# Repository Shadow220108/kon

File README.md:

<h1 align="center">
<br>

<br>
kon
<br>
</h1>

<h3 align="center">

A little ESP32-S3 e-ink reader for books on a microSD card 

</h3>

<div align="center">

</div>

kon is a small e-reader I designed from scratch. It has a 4.26 inch 800 x 480 e-ink screen, reads .txt books off a microSD card, and you flip pages with 4 buttons on the side. It runs off a LiPo battery that charges over USB-C, and since e-ink only uses power when the page changes, the battery lasts ages. The PCB is made in KiCad and the case in Fusion 360.

The render was designed in blender :p

## Journals
Journals were written after I was done with the project with my best memory and a help of AI, it has a total of about 46 hours! 

## Features

- ESP32-S3-WROOM-1-N16R8, 16MB flash, 8MB PSRAM, WiFi and Bluetooth, native USB
- 4.26 inch GDEY0426T82 e-paper (800 x 480, SSD1677) on a 24 pin FPC
- On board high voltage boost circuit for the e-paper
- microSD in 4 bit mode, with its own power switch so it's fully off in sleep
- PREV, NEXT, MENU and BACK buttons that can wake it from deep sleep
- Single cell LiPo with an MCP73831 charger (500mA), red / green charge LEDs
- Power path that runs from USB when plugged in and from the battery when not
- Slide power switch and a TLV75533 low dropout 3.3V regulator
- Battery voltage and USB detect so the firmware can show the battery percent
- USB-C with ESD protection and a 500mA fuse
- 3D printed case with button caps and the kon logo on the back

## Schematic

| Full schematic |
| --- |
|  |

| USB-C | Charger and power path |
| --- | --- |
|  |  |

| Power switch and 3.3V | Battery and sensing |
| --- | --- |
|  |  |

| ESP32-S3 | Reset, boot and buttons |
| --- | --- |
|  |  |

| E-paper interface | microSD |
| --- | --- |
|  |  |

## PCB

The board is 84 x 128 mm with 2 layers, and 4 M2.5 mounting holes. 

| Placement | Fully routed |
| --- | --- |
|  |  |

| E-paper routing | microSD routing | Power routing |
| --- | --- | --- |
|  |  |  |

| Top pour | Bottom pour |
| --- | --- |
|  |  |

Both layers have a ground pour, with a keep-out under the ESP32 antenna on both. Power traces are 0.5 and 0.6 mm, signals 0.25 mm.

| Render back | Render front |
| --- | --- |
|  |  |

## Case

| Front | Side | Back |
| --- | --- | --- |
|  |  |  |

A back tray that the PCB and battery sit in, and a front frame with a window for the screen and 4 button caps. There are cutouts on the side for the USB-C and the power switch. 

## Firmware

The firmware is in `firmware/kon_reader`, written in Arduino with the ESP32 core and GxEPD2.

- Put .txt files in the root of the microSD card
- MENU opens the library, PREV / NEXT move, BACK opens a book
- In a book, PREV / NEXT turn the page and BACK goes back to the library
- It remembers the page you were on for every book
- Battery percent at the bottom, with a + when charging
- After 3 minutes it cuts power to the SD card and goes into deep sleep, any button wakes it up

The firmware was written with the help of AI. I went through it and double checked every pin against the schematic, but it hasn't been tested on the real board yet, so some things might need tweaking.

To flash it, install the "esp32" board package by Espressif and the GxEPD2 library, pick "ESP32S3 Dev Module" with 16MB flash, OPI PSRAM and USB CDC On Boot enabled, hold BOOT, tap RESET and upload over USB-C.

## Why was it made?

I read a lot on my phone and my eyes always hurt after, so I wanted my own e-reader. Making one myself with my own board and case was way more fun than buying one :D

## BOM

| Designator | Value | Part | Qty | Unit Price ($) | Total ($) |
| --- | --- | --- | --- | --- | --- |
| C1 | 4.7nF 0603 | CL10B472KB8NNNC | 1 | 0.0021 | 0.0021 |
| C10 | 22uF 0805 | CL21A226MAQNNNE | 1 | 0.0213 | 0.0213 |
| C7-C9, C11, C13-C16, C28, C30 | 100nF 0603 | CL10B104KB8NNNC | 10 | 0.0036 | 0.0360 |
| C12, C25-C27 | 1uF 0603 | CL10A105KB8NNNC | 4 | 0.0046 | 0.0184 |
| C2, C3, C17 | 4.7uF 0603 | CL10A475KO8NNNC | 3 | 0.0081 | 0.0243 |
| C18-C24 | 1uF 50V 0805 | CL21B105KBFNNNE | 7 | 0.0118 | 0.0826 |
| C4-C6, C29 | 10uF 0805 | CL21A106KAYNNNE | 4 | 0.0162 | 0.0648 |
| D1 | Red LED 0603 | KT-0603R | 1 | 0.0121 | 0.0121 |
| D2 | Green LED 0603 | KT-0603G | 1 | 0.0124 | 0.0124 |
| D3 | Schottky | B5819W | 1 | 0.0150 | 0.0150 |
| D4, D5, D6 | Schottky | MBR0530T1G | 3 | 0.0310 | 0.0930 |
| F1 | 500mA polyfuse 1206 | SMD1206P050TF | 1 | 0.0298 | 0.0298 |
| J1 | USB-C | TYPE-C-31-M-12 | 1 | 0.0975 | 0.0975 |
| J2 | LiPo connector | S2B-PH-SM4-TB | 1 | 0.1172 | 0.1172 |
| J3 | 24 pin FPC | FH12-24S-0.5SH(55) | 1 | 0.3876 | 0.3876 |
| J4 | microSD slot | DM3AT-SF-PEJM5 | 1 | 0.7732 | 0.7732 |
| L1 | 10uH inductor | SRN4018-100M | 1 | 0.1857 | 0.1857 |
| Q1, Q3 | P-MOSFET | AO3401A | 2 | 0.0446 | 0.0892 |
| Q2 | N-MOSFET | SI1308EDL-T1-GE3 | 1 | 0.1169 | 0.1169 |
| R1, R2 | 5.1k 0603 | RC0603FR-075K1L | 2 | 0.0013 | 0.0026 |
| R7, R10, R11, R14-R17, R24 | 100k 0603 | RC0603FR-07100KL | 8 | 0.0013 | 0.0104 |
| R12, R13, R19-R23 | 10k 0603 | RC0603FR-0710KL | 7 | 0.0013 | 0.0091 |
| R18 | 2.2R 0603 | RC0603FR-072R2L | 1 | 0.0015 | 0.0015 |
| R3, R8, R9 | 1M 0603 | RC0603FR-071ML | 3 | 0.0013 | 0.0039 |
| R4 | 2k 0603 | RC0603FR-072KL | 1 | 0.0013 | 0.0013 |
| R5, R6 | 1k 0603 | RC0603FR-071KL | 2 | 0.0013 | 0.0026 |
| SW1 | Slide switch | PCM12SMTR | 1 | 0.7199 | 0.7199 |
| SW2, SW3 | Tactile switch | PTS810SJM250SMTRLFS | 2 | 0.1980 | 0.3960 |
| SW4-SW7 | Tactile switch | PTS645SM43SMTR92 | 4 | 0.2432 | 0.9728 |
| U1 | ESP32-S3 module | ESP32-S3-WROOM-1-N16R8 | 1 | 3.4726 | 3.4726 |
| U2 | USB ESD | USBLC6-2SC6 | 1 | 0.0796 | 0.0796 |
| U3 | LiPo charger | MCP73831T-2ACI/OT | 1 | 0.4665 | 0.4665 |
| U4 | 3.3V LDO | TLV75533PDBVR | 1 | 0.0680 | 0.0680 |
| Display | 4.26in e-paper 800x480 | GDEY0426T82 | 1 | 32.0000 | 32.0000 |
| Battery | 3.7V 2000mAh LiPo, JST-PH | Adafruit 2011 | 1 | 12.5000 | 12.5000 |
| | Components | | | | 52.89 |
| | PCBA (2 boards, JLCPCB) | | 1 | 76.00 | 76.00 |
| | Total | | | | 128.89 |

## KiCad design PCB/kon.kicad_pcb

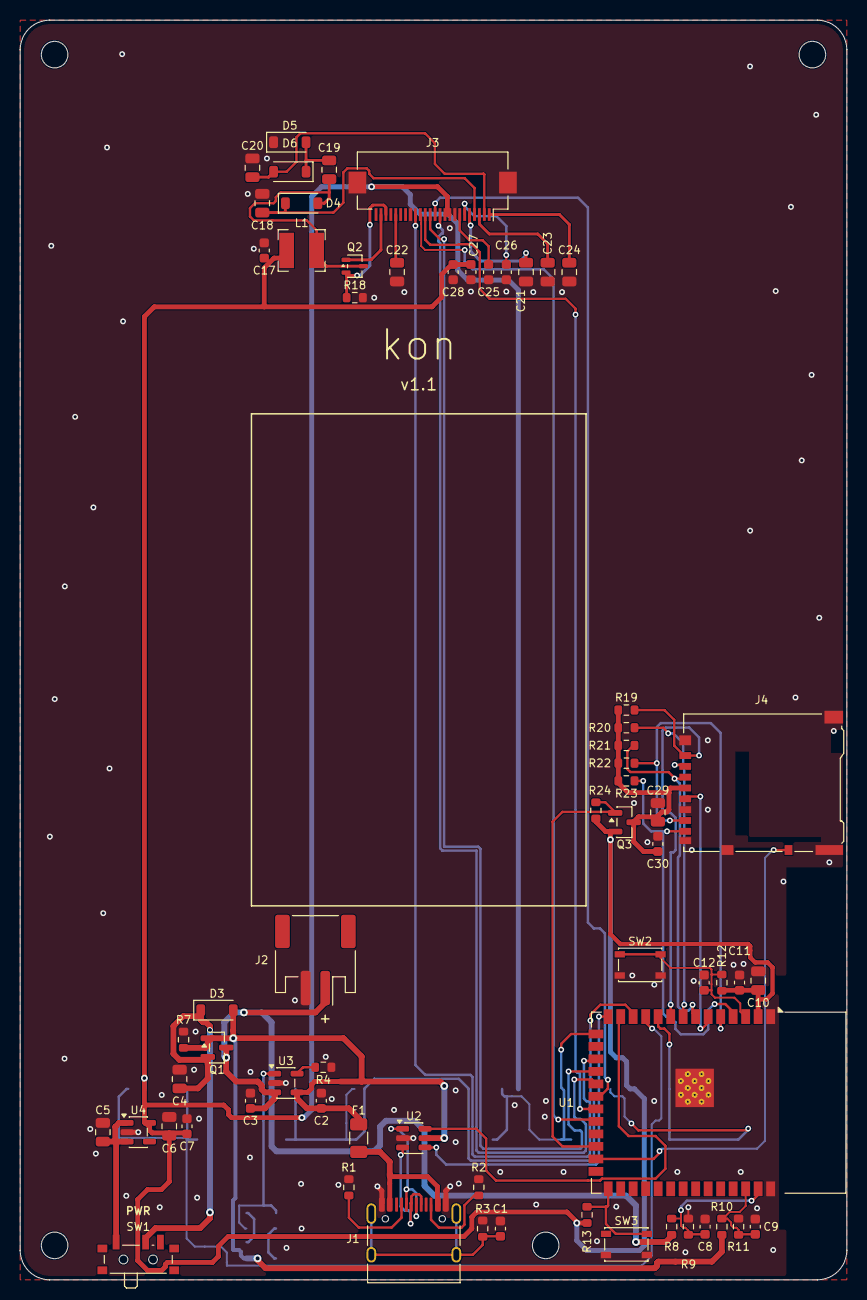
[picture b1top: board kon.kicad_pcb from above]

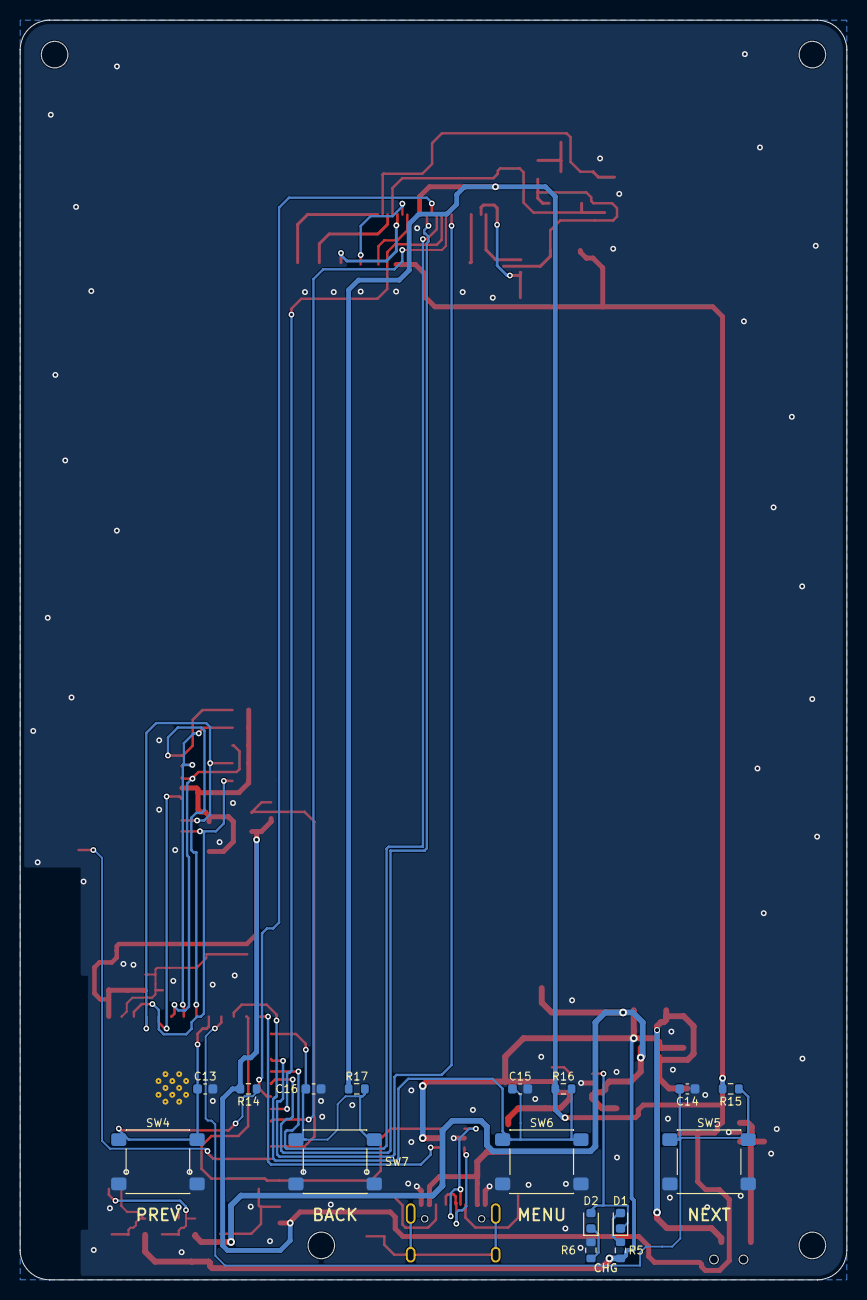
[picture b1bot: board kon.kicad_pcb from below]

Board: 2 copper layers, 84.0 x 128.0 mm, 85 parts (17 on the bottom side), 53 nets.

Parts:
C1: 4.7n; C_0603_1608Metric
C2, C3, C17: 4.7u; C_0603_1608Metric
C4, C5, C6, C29: 10u; C_0805_2012Metric
C7, C8, C9, C11, C13, C14, C15, C16, C28, C30: 100n; C_0603_1608Metric
C10: 22u; C_0805_2012Metric
C12, C25, C26, C27: 1u; C_0603_1608Metric
C18, C19, C20, C21, C22, C23, C24: 1u/50V; C_0805_2012Metric
D1: RED; LED_0603_1608Metric
D2: GREEN; LED_0603_1608Metric
D3: B5819W; D_SOD-123
D4, D5, D6: MBR0530; D_SOD-123
DS1: GDEY0426T82; EPD_GDEY0426T82
F1: 500mA; Fuse_1206_3216Metric
H1, H2, H3, H4: M2.5; MountingHole_2.7mm_M2.5
J1: USB-C; USB_C_Receptacle_HRO_TYPE-C-31-M-12
J2: LiPo 1S; JST_PH_S2B-PH-SM4-TB_1x02-1MP_P2.00mm_Horizontal
J3: EPD FPC 24P; Hirose_FH12-24S-0.5SH_1x24-1MP_P0.50mm_Horizontal
J4: microSD; microSD_HC_Hirose_DM3AT-SF-PEJM5
L1: 10u; L_Bourns-SRN4018
Q1, Q3: AO3401A; SOT-23
Q2: Si1308EDL; SOT-323_SC-70
R1, R2: 5.1k; R_0603_1608Metric
R3, R8, R9: 1M; R_0603_1608Metric
R4: 2k; R_0603_1608Metric
R5, R6: 1k; R_0603_1608Metric
R7, R10, R11, R14, R15, R16, R17, R24: 100k; R_0603_1608Metric
R12, R13, R19, R20, R21, R22, R23: 10k; R_0603_1608Metric
R18: 2.2; R_0603_1608Metric
SW1: PWR; SW_SPDT_PCM12
SW2: RESET; SW_SPST_PTS810
SW3: BOOT; SW_SPST_PTS810
SW4: PREV; SW_SPST_PTS645Sx43SMTR92
SW5: NEXT; SW_SPST_PTS645Sx43SMTR92
SW6: MENU; SW_SPST_PTS645Sx43SMTR92
SW7: BACK; SW_SPST_PTS645Sx43SMTR92
U1: ESP32-S3-WROOM-1-N16R8; ESP32-S3-WROOM-1
U2: USBLC6-2SC6; SOT-23-6
U3: MCP73831-2-OT; SOT-23-5
U4: TLV75533PDBV; SOT-23-5

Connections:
+3V3: C6.1, C7.1, C10.1, C11.1, C17.1, C27.1, C28.1, J3.9, J3.10, L1.1, Q3.2, R12.1, R13.1, R14.1, R15.1, R16.1, R17.1, R24.1, U1.2, U4.5
+BATT: C3.1, J2.1, Q1.3, R8.1, U3.3
+VSW: C5.1, SW1.1, U4.1, U4.3
/BOOT: R13.2, SW3.1, U1.27
/BTN_BACK: C16.1, R17.2, SW7.1, U1.15
/BTN_MENU: C15.1, R16.2, SW6.1, U1.12
/BTN_NEXT: C14.1, R15.2, SW5.1, U1.11
/BTN_PREV: C13.1, R14.2, SW4.1, U1.10
/CC1: J1.A5, R1.1
/CC2: J1.B5, R2.1
/EN: C12.1, R12.2, SW2.1, U1.3
/EPD_BUSY: J3.16, U1.17
/EPD_CS: J3.13, U1.18
/EPD_DC: J3.14, U1.21
/EPD_GDR: J3.23, Q2.1
/EPD_MOSI: J3.11, U1.19
/EPD_RESE: J3.22, Q2.2, R18.1
/EPD_RST: J3.15, U1.22
/EPD_SCK: J3.12, U1.20
/EPD_VCOM: C24.1, J3.1
/EPD_VDD: C25.1, J3.7
/EPD_VGH: C18.1, D4.1, J3.4
/EPD_VGL: C20.1, D6.2, J3.2
/EPD_VPP: C26.1, J3.6
/EPD_VSH1: C21.1, J3.5
/EPD_VSH2: C22.1, J3.20
/EPD_VSL: C23.1, J3.3
/SD_CLK: J4.5, U1.6
/SD_CMD: J4.3, R21.2, U1.7
/SD_D0: J4.7, R22.2, U1.5
/SD_D1: J4.8, R23.2, U1.4
/SD_D2: J4.1, R19.2, U1.9
/SD_D3: J4.2, R20.2, U1.8
/SD_DET: J4.10, U1.25
/SD_EN: Q3.1, R24.2, U1.24
/SD_VDD: C29.1, C30.1, J4.4, Q3.3, R19.1, R20.1, R21.1, R22.1, R23.1
/USB_D+: U1.14, U2.4
/USB_D-: U1.13, U2.6
/USB_SH: C1.1, J1.SH, R3.1
/VBAT_ADC: C8.1, R8.2, R9.1, U1.39
/VBUS_DET: C9.1, R10.2, R11.1, U1.38
/VSYS: C4.1, D3.1, Q1.2, SW1.2
GND: C1.2, C2.2, C3.2, C4.2, C5.2, C6.2, C7.2, C8.2, C9.2, C10.2, C11.2, C12.2, C13.2, C14.2, C15.2, C16.2, C17.2, C18.2, C20.2, C21.2, C22.2, C23.2, C24.2, C25.2, C26.2, C27.2, C28.2, C29.2, C30.2, D5.1, J1.A1, J1.A12, J1.B1, J1.B12, J2.2, J3.8, J3.17, J3.MP, J4.6, J4.9, J4.SH, R1.2, R2.2, R3.2, R4.2, R6.2, R7.2, R9.2, R11.2, R18.2, SW2.2, SW3.2, SW4.2, SW5.2, SW6.2, SW7.2, U1.1, U1.40, U1.41, U2.2, U3.2, U4.2
unnamed: D1.2, R5.2
unnamed: D1.1, D2.2, U3.1
unnamed: D2.1, R6.1
unnamed: C19.1, D4.2, L1.2, Q2.3
unnamed: C19.2, D5.2, D6.1
unnamed: F1.1, J1.A4, J1.A9, J1.B4, J1.B9
unnamed: J1.A6, J1.B6, U2.3
unnamed: J1.A7, J1.B7, U2.1
unnamed: R4.1, U3.5
VBUS: C2.1, D3.2, F1.2, Q1.1, R5.1, R7.1, R10.1, U2.5, U3.4

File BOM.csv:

Designator,Value,Part,Qty,Unit Price ($),Total ($)
C1,4.7nF 0603,CL10B472KB8NNNC,1,0.0021,0.0021
C10,22uF 0805,CL21A226MAQNNNE,1,0.0213,0.0213
"C7-C9, C11, C13-C16, C28, C30",100nF 0603,CL10B104KB8NNNC,10,0.0036,0.0360
"C12, C25-C27",1uF 0603,CL10A105KB8NNNC,4,0.0046,0.0184
"C2, C3, C17",4.7uF 0603,CL10A475KO8NNNC,3,0.0081,0.0243
C18-C24,1uF 50V 0805,CL21B105KBFNNNE,7,0.0118,0.0826
"C4-C6, C29",10uF 0805,CL21A106KAYNNNE,4,0.0162,0.0648
D1,Red LED 0603,KT-0603R,1,0.0121,0.0121
D2,Green LED 0603,KT-0603G,1,0.0124,0.0124
D3,Schottky,B5819W,1,0.0150,0.0150
"D4, D5, D6",Schottky,MBR0530T1G,3,0.0310,0.0930
F1,500mA polyfuse 1206,SMD1206P050TF,1,0.0298,0.0298
J1,USB-C,TYPE-C-31-M-12,1,0.0975,0.0975
J2,LiPo connector,S2B-PH-SM4-TB,1,0.1172,0.1172
J3,24 pin FPC,FH12-24S-0.5SH(55),1,0.3876,0.3876
J4,microSD slot,DM3AT-SF-PEJM5,1,0.7732,0.7732
L1,10uH inductor,SRN4018-100M,1,0.1857,0.1857
"Q1, Q3",P-MOSFET,AO3401A,2,0.0446,0.0892
Q2,N-MOSFET,SI1308EDL-T1-GE3,1,0.1169,0.1169
"R1, R2",5.1k 0603,RC0603FR-075K1L,2,0.0013,0.0026
"R7, R10, R11, R14-R17, R24",100k 0603,RC0603FR-07100KL,8,0.0013,0.0104
"R12, R13, R19-R23",10k 0603,RC0603FR-0710KL,7,0.0013,0.0091
R18,2.2R 0603,RC0603FR-072R2L,1,0.0015,0.0015
"R3, R8, R9",1M 0603,RC0603FR-071ML,3,0.0013,0.0039
R4,2k 0603,RC0603FR-072KL,1,0.0013,0.0013
"R5, R6",1k 0603,RC0603FR-071KL,2,0.0013,0.0026
SW1,Slide switch,PCM12SMTR,1,0.7199,0.7199
"SW2, SW3",Tactile switch,PTS810SJM250SMTRLFS,2,0.1980,0.3960
SW4-SW7,Tactile switch,PTS645SM43SMTR92,4,0.2432,0.9728
U1,ESP32-S3 module,ESP32-S3-WROOM-1-N16R8,1,3.4726,3.4726
U2,USB ESD,USBLC6-2SC6,1,0.0796,0.0796
U3,LiPo charger,MCP73831T-2ACI/OT,1,0.4665,0.4665
U4,3.3V LDO,TLV75533PDBVR,1,0.0680,0.0680
Display,4.26in e-paper 800x480,GDEY0426T82,1,32.0000,32.0000
Battery,"3.7V 2000mAh LiPo, JST-PH",Adafruit 2011,1,12.5000,12.5000
,Components,,,,52.89
,"PCBA (2 boards, JLCPCB)",,1,76.00,76.00
,Total,,,,128.89

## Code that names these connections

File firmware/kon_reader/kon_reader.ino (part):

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
// ---------------- pins (from the schematic) ----------------
// e-paper
#define EPD_BUSY  9
#define EPD_CS    10
#define EPD_MOSI  11
#define EPD_SCK   12
#define EPD_DC    13
#define EPD_RST   14

// microSD (4 bit SD_MMC)
#define SD_D1     4
#define SD_D0     5
#define SD_CLK    6
#define SD_CMD    7
#define SD_D3     15
#define SD_D2     16
#define SD_EN     47   // P-MOSFET gate, LOW = card powered
#define SD_DET    48   // LOW = card inserted

// buttons (100k pull-up, pressed = LOW)
#define BTN_BACK  3
#define BTN_MENU  8
#define BTN_PREV  17
#define BTN_NEXT  18

// sensing
#define VBAT_ADC  1    // 1M / 1M divider, battery / 2
#define VBUS_DET  2    // 100k / 100k divider, HIGH when USB is plugged in

// ---------------- display ----------------
// paged drawing, 1/4 of the screen at a time so it fits in RAM easily
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
// ---------------- sd card ----------------
bool startSD() {
  pinMode(SD_EN, OUTPUT);
  digitalWrite(SD_EN, LOW);       // power the card
  delay(20);
  if (digitalRead(SD_DET) == HIGH) return false;   // no card
  SD_MMC.setPins(SD_CLK, SD_CMD, SD_D0, SD_D1, SD_D2, SD_D3);
  return SD_MMC.begin("/sdcard", false);           // 4 bit mode
}

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// ---------------- setup / loop ----------------
void setup() {
  Serial.begin(115200);
  pinMode(BTN_BACK, INPUT);
  pinMode(BTN_MENU, INPUT);
  pinMode(BTN_PREV, INPUT);
  pinMode(BTN_NEXT, INPUT);
  pinMode(SD_DET, INPUT_PULLUP);
  pinMode(VBUS_DET, INPUT);
  analogReadResolution(12);

  SPI.begin(EPD_SCK, -1, EPD_MOSI, EPD_CS);
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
